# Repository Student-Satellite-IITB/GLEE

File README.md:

# GLEE
## Spectroscopy Payload
**Aim -** To validate the presence of minerals in the lunar regolith through gamma ray or x-ray spectroscopy.

**Tasks:**
- Designing a capable spectroscopy system
- Testing the precision of spectral lines
- Modelling known sources of radiation and their spectrum
- Data analysis and inference
### Circuit Design

The Circuit Consists of the following parts-
- Diode Sensor & Voltage Bias
- Charge Sensitive Preamplifier
- Pulse Shaper Circuit
- Baseline Restorer & Pole-Zero Cancellation
- Amplifier
- Multi-Channel Analyzer

### Diode Sensor

The X-rays and gamma rays coming from Sun, hit the lunar surface and are reflected by the lunar regolith. The photons from the reflected rays hit our sensor and produce a surge in the reverse current. The magnitude of this surge is used to estimate the composition of the lunar soil. We have decided to use photodiode sensors for the the task due to lower power consumption and small size as compared to other detectors. 

After going through the response rates of various diodes, the following 2 photodiode detectors were finalized:
- UM 9441: https://www.microsemi.com/existing-parts/parts/82558#resources
- X1007: https://www.mouser.in/datasheet/2/313/FirstSensor_09202018_X100-7_SMD_501401-1483097.pdf

While UM9441 is a radiation hardened diode, X1007 has prior spectroscopy usage. Both diodes need to have a reverse biased voltage of around 30 V in order to act as photodiode. 
The output voltage from the GLEE solar panel is expected to be 5 V, hence a boost convertor would be required to step up the voltage from 5 V to 30 V.

Selected Boost Convertor: **TPS6104x-Q1**  (https://www.ti.com/document-viewer/TPS61041-Q1/datasheet).
This boost convertor can step up voltage from 5 V to 28 V with an efficiency of 85 %, which was highest among the converters seen.

### Charge Sensitive Preamplifier

The next component in our system is the charge sensitive preamplifier, its task is to convert the current signal coming from the photodiode to a voltage signal which is easier to process and amplify. The output current from the photodiode is a **pulse train of dirac-delta signals** with each pulse representig an individual photon hitting the photodiode sensor. This current signal acts as the input signal for the CSP. The output of the CSP depends on the charge accumulated on it due to the photocurrent. The CSP can be thought as an integrator having current input and charge based voltage output.

The preamplifier basically consists of an Opamp, a pair of capacitors and a discharging mechanism. The CSP needs to regularly discharged in order to prevent it from getting saturated and/or saturating the final diode. We are using a resistance feedback CSP which uses the feedback resistance of the opamp to continously discharge the capacitor. The output voltage of this CSP is a **pulse train of exponential signals**. The height of each signal is directly propotional to the energy of the incident photons and time constant for this exponential signal is as per the values of feedback resistance and capacitance. The values of our feedback components are based on the count rate of the radiation. 

Count rate of a radiation for any sensor refers to the number of photons belonging to the energy range of that radiation that are hitting the sensor in a second.
- Count rate of X-rays = 
- Count rate of Gamma rays =

The time constant for the CSP has to be lesser than the one-fifth of the maximum count rate possible. For the CSP designed by us-
- Feedback Resistance (R) =
- Feedback Capacitance (C) =
- Time Constant (RC) =

Another possible alternative to this RF CSP would have been the transistor reset pre-amplifier, but it was rejected due to excessively complicated circuitry, higher power & size as compared to RF CSP and no significant benefits other than slight reduced noise.

Present COTS Opamp Models shortlisted for CSP-
- OPA656 : https://www.ti.com/document-viewer/OPA656/datasheet
- LMH6626 : https://www.ti.com/document-viewer/LMH6626/datasheet

### Pulse Shaper Circuit
The sensor is susceptible to noise and various forms of disturbances that cause deformation in the signal, therefore the signal needs to be filtered before it is sent to the amplifier in order to prevent amplification of unnecessary noise. The Pulse Shaper is basically a bandpass filter responsible for removing both the low and high frequency noises along with shaping the voltage signal in order to allow easier amplification and digitization. The input of the Pulse shaper is an **exponential voltage signal** obtained from CSP and the output is an **Gaussian voltage pulse**. A Gaussian shape minimizes the noise along with allowing easier digitization.

Our Pulse Shaper Circuit consists of one differentiator (high pass filter) and four integrators (low pass filter), with each of these sperated by a voltage follower in order to not cause any influence on each other. Use of four integrators as compared to one, significantly increases the shaping precision and therefore its recommended. Even 8 integrators may be used but were avoided in order to not further increase the size of circuit. The time constant of the integrators and the differentiators depend on the CSP time constant, and hence on the count rate of radiation. We have kept the sum of time constant of integrator same as that of the differentiator and the CSP. The exact values of capacitors and resistors used for this configuration were obtained after a lot of trial and error, until we were able to obtain optimum shaping. 
- Time Constant of integrators =
- Time Constant of differentiator =

The COTS components that we can use to build our Pulse Shaper :
- UA741 : https://www.ti.com/document-viewer/UA741/datasheet/features-slos0946106#SLOS0946106
- LM310 : https://circuits-diy.com/wp-content/uploads/2021/01/LM310N.pdf
- OP07 : https://www.ti.com/document-viewer/OP07/datasheet

### Baseline Restorer & Pole-Zero Cancellation
The Baseline restorer and pole-zero cancellation are not independent components but are additions to the pulse shaper in order to tackle the issues arising from the non idealities in the opamps that may lead to baseline shift, which is a constant offset voltage in addition to the required signal or it may cause ringing that leads to the signal not being able to reach a fixed value and keep oscillating around it.

to tackle such issues we have implemented these two corrective measures. The Pole zero restoration has been implemented alongside the differentiator with an extra resistance being added parallely to the capacitor there, meanwhile the baseline restorer requires an Opamp that  provides a negative feedbacks to any constant voltage present in the output signal and thus reducing it to zero.

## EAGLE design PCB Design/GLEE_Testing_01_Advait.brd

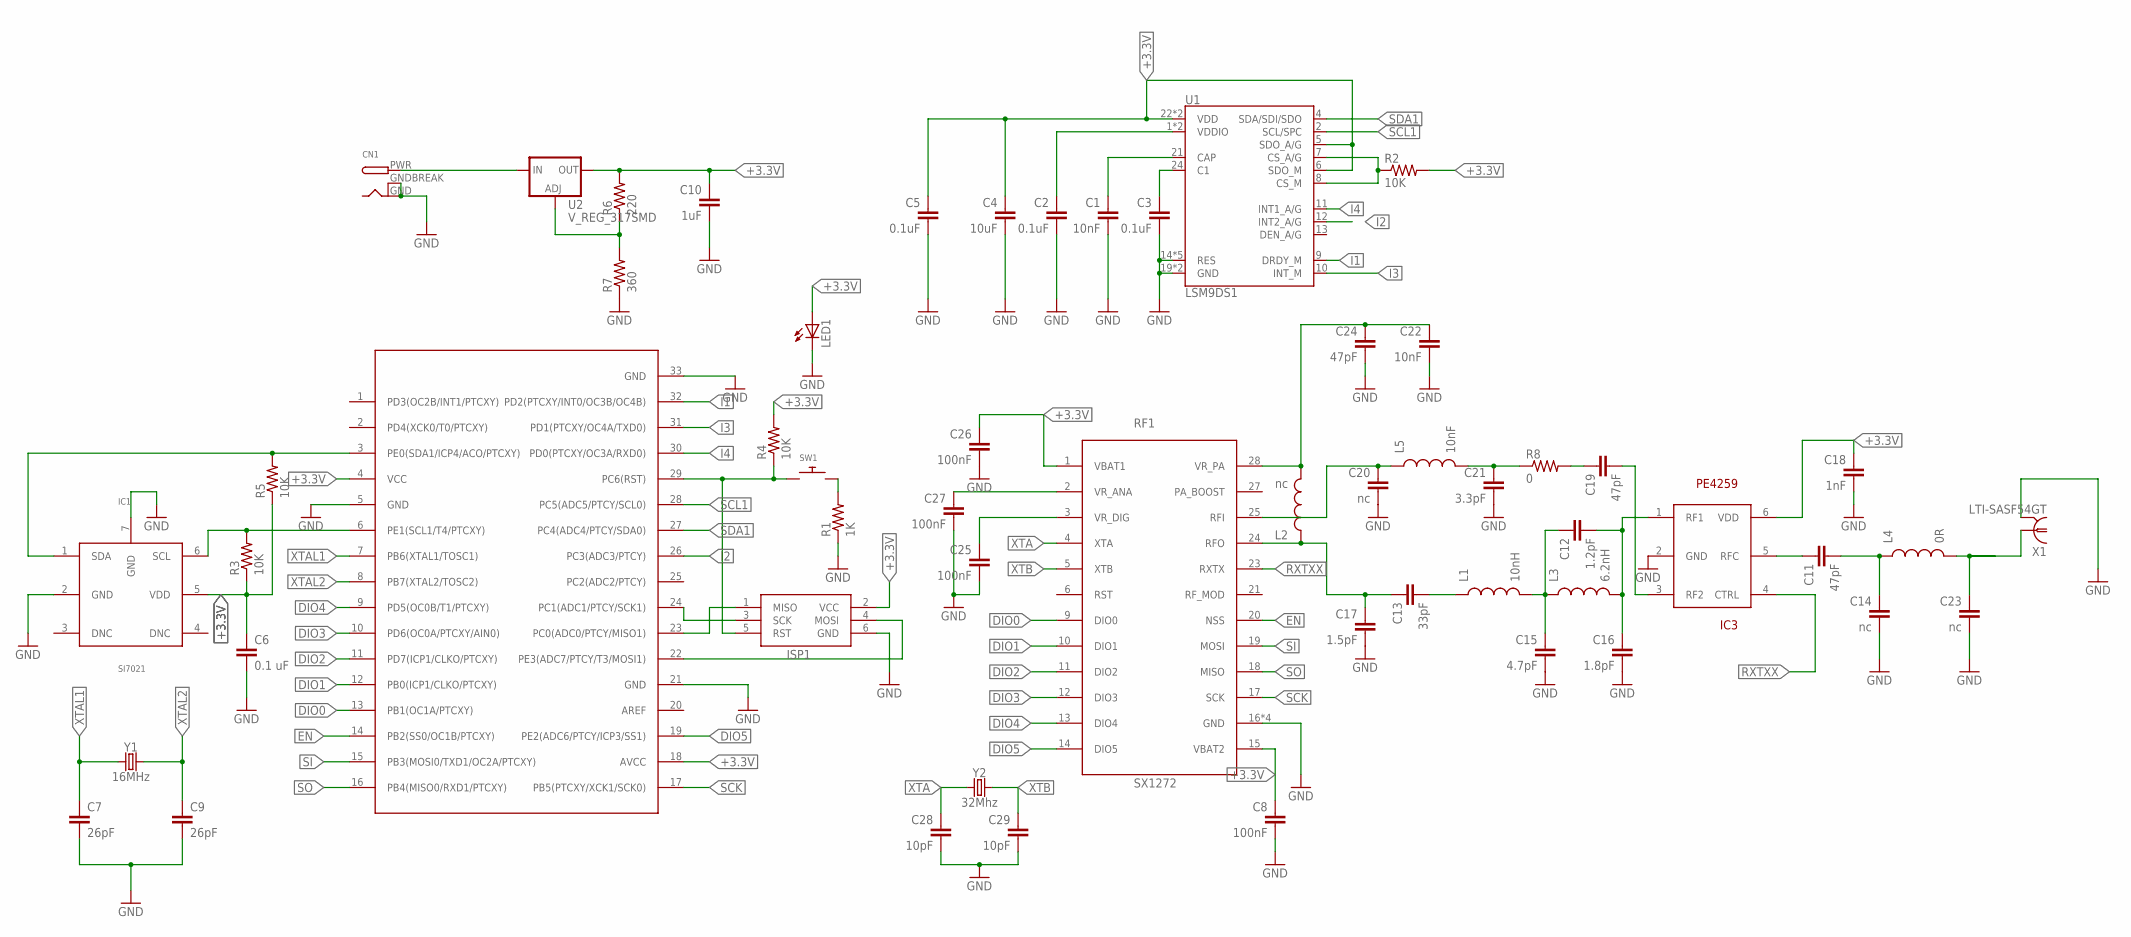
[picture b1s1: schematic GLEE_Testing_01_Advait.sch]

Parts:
C1, C22: 10nF; 0402-CAP
C2, C3, C5: 0.1uF; 0402-CAP
C4: 10uF; 0402-CAP
C6: 0.1 uF; 0402-CAP
C7, C9: 26pF; 0402-CAP
C8, C25, C26, C27: 100nF; 0402-CAP
C10: 1uF; 0402-CAP
C11, C19, C24: 47pF; 0402-CAP
C12: 1.2pF; 0402-CAP
C13: 33pF; 0402-CAP
C14, C20, C23: nc; 0402-CAP
C15: 4.7pF; 0402-CAP
C16: 1.8pF; 0402-CAP
C17: 1.5pF; 0402-CAP
C18: 1nF; 0402-CAP
C21: 3.3pF; 0402-CAP
C28, C29: 10pF; 0402-CAP
CN1: DCBARRELPTH; DCJACK_2MM_PTH
IC1: SI7021
IC2: ATMEGA328-PB
IC3: PE4259
ISP1: AVRISP-6; AVRISP
L1: 10nH; C0402
L2: nc; C0402
L3: 6.2nH; C0402
L4: 0R; C0402
L5: 10nF; C0402
LED1: LEDCHIPLED_0805; CHIPLED_0805
R1: 1K; 0402-RES
R2, R3, R4, R5: 10K; 0402-RES
R6: 220; 0402-RES
R7: 360; 0402-RES
R8: 0; 0402-RES
RF1: SX1272
SW1: SWITCH_PUSHBUTTONSOFTTOUCHSMD_SJ; PUSHBUTTON_SMD_SJ
U1: LSM9DS1; LGA24-8X4
U2: V_REG_317SMD; SOT223
X1: LTI-SASF54GT
Y1: 16MHz; CRYSTAL-SMD-2.0X1.6MM
Y2: 32Mhz; CRYSTAL-SMD-2.0X1.6MM

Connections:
DIO0: IC2.13 (PB1(OC1A/PTCXY)), RF1.9 (DIO0)
DIO1: IC2.12 (PB0(ICP1/CLKO/PTCXY)), RF1.10 (DIO1)
DIO2: IC2.11 (PD7(ICP1/CLKO/PTCXY)), RF1.11 (DIO2)
DIO3: IC2.10 (PD6(OC0A/PTCXY/AIN0)), RF1.12 (DIO3)
DIO4: IC2.9 (PD5(OC0B/T1/PTCXY)), RF1.13 (DIO4)
DIO5: IC2.19 (PE2(ADC6/PTCY/ICP3/SS1)), RF1.14 (DIO5)
EN: IC2.14 (PB2(SS0/OC1B/PTCXY)), RF1.20 (NSS)
GND: C1.2, C2.2, C3.2, C4.2, C5.2, C6.2, C7.2, C8.2, C9.2, C10.2, C14.2, C15.2, C16.2, C17.2, C18.2, C20.2, C21.2, C22.2, C23.2, C24.2, C25.2, C26.2, C27.2, C28.2, C29.2, CN1.GND, CN1.GNDBREAK, IC1.2 (GND), IC1.7 (GND), IC2.5 (GND), IC2.21 (GND), IC2.33 (GND), IC3.2 (GND), ISP1.6 (GND), LED1.C, R1.1, R7.1, RF1.16 (GND), RF1.22 (GND), RF1.26 (GND), RF1.29 (GND), U1.14 (RES), U1.15 (RES), U1.16 (RES), U1.17 (RES), U1.18 (RES), U1.19 (GND), U1.20 (GND), X1.2, X1.3 (2), X1.4 (2), X1.5 (2); also elsewhere on the board
I1: IC2.32 (PD2(PTCXY/INT0/OC3B/OC4B)), U1.9 (DRDY_M)
I2: IC2.26 (PC3(ADC3/PTCY)), U1.12 (INT2_A/G)
I3: IC2.31 (PD1(PTCXY/OC4A/TXD0)), U1.10 (INT_M)
I4: IC2.30 (PD0(PTCXY/OC3A/RXD0)), U1.11 (INT1_A/G)
unnamed: C19.1, R8.2
unnamed: C22.1, C24.1, L2.2, RF1.28 (VR_PA)
unnamed: CN1.PWR, U2.3 (IN)
unnamed: C19.2, IC3.3 (RF2)
unnamed: R2.1, U1.7 (CS_A/G), U1.8 (CS_M)
unnamed: R6.1, R7.2, U2.1 (ADJ)
unnamed: C20.1, L5.1, RF1.25 (RFI)
unnamed: C1.1, U1.21 (CAP)
unnamed: C2.1, U1.1 (VDDIO), U1.3 (VDDIO)
unnamed: C21.1, L5.2, R8.1
unnamed: C13.1, C17.1, L2.1, RF1.24 (RFO)
unnamed: C12.1, C15.1, L1.2, L3.1
unnamed: C13.2, L1.1
unnamed: C12.2, C16.1, IC3.1 (RF1), L3.2
unnamed: C23.1, L4.2, X1.1
unnamed: C11.1, IC3.5 (RFC)
unnamed: C3.1, U1.24 (C1)
unnamed: C11.2, C14.1, L4.1
unnamed: IC2.29 (PC6(RST)), ISP1.5 (RST), R4.1, SW1.P$1
unnamed: IC2.24 (PC1(ADC1/PTCY/SCK1)), ISP1.3 (SCK)
unnamed: C27.1, RF1.2 (VR_ANA)
unnamed: C25.1, RF1.3 (VR_DIG)
unnamed: IC2.23 (PC0(ADC0/PTCY/MISO1)), ISP1.1 (MISO)
unnamed: IC2.22 (PE3(ADC7/PTCY/T3/MOSI1)), ISP1.4 (MOSI)
unnamed: R1.2, SW1.P$2
RXTXX: IC3.4 (CTRL), RF1.23 (RXTX)
SCK: IC2.17 (PB5(PTCXY/XCK1/SCK0)), RF1.17 (SCK)
SCL: IC1.6 (SCL), IC2.6 (PE1(SCL1/T4/PTCXY)), R3.2
SCL1: IC2.28 (PC5(ADC5/PTCY/SCL0)), U1.2 (SCL/SPC)
SDA: IC1.1 (SDA), IC2.3 (PE0(SDA1/ICP4/ACO/PTCXY)), R5.2
SDA1: IC2.27 (PC4(ADC4/PTCY/SDA0)), U1.4 (SDA/SDI/SDO)
SI: IC2.15 (PB3(MOSI0/TXD1/OC2A/PTCXY)), RF1.19 (MOSI)
SO: IC2.16 (PB4(MISO0/RXD1/PTCXY)), RF1.18 (MISO)
XTA: C28.1, RF1.4 (XTA), Y2.1
XTAL1: C7.1, IC2.7 (PB6(XTAL1/TOSC1)), Y1.1
XTAL2: C9.1, IC2.8 (PB7(XTAL2/TOSC2)), Y1.3 (2)
XTB: C29.1, RF1.5 (XTB), Y2.3 (2)

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
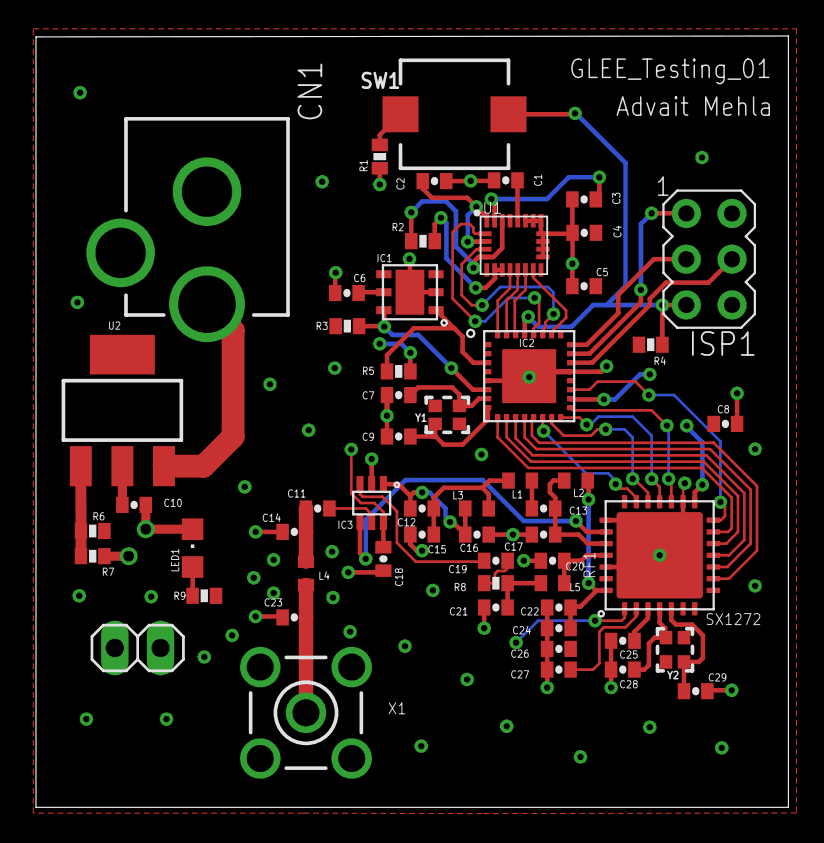
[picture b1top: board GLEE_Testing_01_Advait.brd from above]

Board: 2 copper layers, 41.8 x 42.9 mm, 57 parts (0 on the bottom side), 51 nets.

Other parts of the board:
JP6: 1X02
R9: 100; 0402-RES

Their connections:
GND: JP6.1; also elsewhere on the board

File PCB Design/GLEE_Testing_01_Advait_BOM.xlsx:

Part | Value | Device | Package | Description | Comments
C1 | 10nF | CAP0402-CAP | 0402-CAP | Capacitor
C2 | 0.1uF | CAP0402-CAP | 0402-CAP | Capacitor
C3 | 0.1uF | CAP0402-CAP | 0402-CAP | Capacitor
C4 | 10uF | CAP0402-CAP | 0402-CAP | Capacitor
C5 | 0.1uF | CAP0402-CAP | 0402-CAP | Capacitor
C6 | 0.1 uF | CAP0402-CAP | 0402-CAP | Capacitor
C7 | 26pF | CAP0402-CAP | 0402-CAP | Capacitor
C8 | 100nF | CAP0402-CAP | 0402-CAP | Capacitor
C9 | 26pF | CAP0402-CAP | 0402-CAP | Capacitor
C10 | 1uF | CAP0402-CAP | 0402-CAP | Capacitor
C11 | 47pF | CAP0402-CAP | 0402-CAP | Capacitor
C12 | 1.2pF | CAP0402-CAP | 0402-CAP | Capacitor
C13 | 33pF | CAP0402-CAP | 0402-CAP | Capacitor
C14 | nc | CAP0402-CAP | 0402-CAP | Capacitor
C15 | 4.7pF | CAP0402-CAP | 0402-CAP | Capacitor
C16 | 1.8pF | CAP0402-CAP | 0402-CAP | Capacitor
C17 | 1.5pF | CAP0402-CAP | 0402-CAP | Capacitor
C18 | 1nF | CAP0402-CAP | 0402-CAP | Capacitor
C19 | 47pF | CAP0402-CAP | 0402-CAP | Capacitor
C20 | nc | CAP0402-CAP | 0402-CAP | Capacitor
C21 | 3.3pF | CAP0402-CAP | 0402-CAP | Capacitor
C22 | 10nF | CAP0402-CAP | 0402-CAP | Capacitor
C23 | nc | CAP0402-CAP | 0402-CAP | Capacitor
C24 | 47pF | CAP0402-CAP | 0402-CAP | Capacitor
C25 | 100nF | CAP0402-CAP | 0402-CAP | Capacitor
C26 | 100nF | CAP0402-CAP | 0402-CAP | Capacitor
C27 | 100nF | CAP0402-CAP | 0402-CAP | Capacitor
C28 | 10pF | CAP0402-CAP | 0402-CAP | Capacitor
C29 | 10pF | CAP0402-CAP | 0402-CAP | Capacitor
CN1 |  | DCBARRELPTH | DCJACK_2MM_PTH | 2.0mm DC Barrel Jack
IC1 | SI7021 | SI7021 | SI7021 - A20
IC2 | ATMEGA328-PB | ATMEGA328-PB | 32-pin 32MS1
IC3 | PE4259 | PE4259 | 6-lead SC-70
ISP1 | AVRISP-6 | AVRISP-6 | AVRISP | AVR ISP HEADER
L1 | 10nH | INDUCTOR0402 | C0402 | Inductors
L2 | nc | INDUCTOR0402 | C0402 | Inductors
L3 | 6.2nH | INDUCTOR0402 | C0402 | Inductors
L4 | 0R | INDUCTOR0402 | C0402 | Inductors | Zero Ohm Resistor
L5 | 10nF | INDUCTOR0402 | C0402 | Inductors
LED1 |  | LEDCHIPLED_0805 | CHIPLED_0805 | LED
R1 | 1K | RESISTOR0402-RES | 0402-RES | Resistor
R2 | 10K | RESISTOR0402-RES | 0402-RES | Resistor
R3 | 10K | RESISTOR0402-RES | 0402-RES | Resistor
R4 | 10K | RESISTOR0402-RES | 0402-RES | Resistor
R5 | 10K | RESISTOR0402-RES | 0402-RES | Resistor
R6 | 220 | RESISTOR0402-RES | 0402-RES | Resistor
R7 | 360 | RESISTOR0402-RES | 0402-RES | Resistor
R8 | 0 | RESISTOR0402-RES | 0402-RES | Resistor
RF1 | SX1272 | SX1272 | 28-lead QFN
SW1 |  | SWITCH_PUSHBUTTONSOFTTOUCHSMD_SJ | PUSHBUTTON_SMD_SJ | Buttons
U1 | LSM9DS1 | LSM9DS1 | LGA24-8X4 | LSM9DS1 3D accelerometer, gyroscope & magnetometer
U2 | V_REG_317SMD | V_REG_317SMD | SOT223 | Voltage Regulator
X1 | LTI-SASF54GT | LTI-SASF54GT | LTI-SASF54GT | SMA vertical PCB through hole jack
Y1 | 16MHz | CRYSTAL-16MHZSMD-2X1.6 | CRYSTAL-SMD-2.0X1.6MM | 16MHz Crystal
Y2 | 32Mhz | CRYSTAL-16MHZSMD-2X1.6 | CRYSTAL-SMD-2.0X1.6MM | 16MHz Crystal

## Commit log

2020-03-14 Added codes for data analysis
    elecentro.dat-Data file of earthquake data
    Project_Elecentro.ipynb-Project codes
    Test_cases.ipynb-Test cases for functions used in project.
2020-04-22 updated codes for seismic responsse spectrum
2021-06-25 Rename README.md to SRS_Elcentro/README.md
2021-06-25 Rename Project_Elecentro.ipynb to SRS_Elcentro/Project_Elecentro.ipynb
2021-06-25 Test cases for functions in shock response spectrum
2021-06-25 Data file used in code
2021-06-27 EW data for elcentro earthquake
2021-06-27 data for elcentro earthquake
2021-06-27 data from phone accelerometer
2021-06-27 Code for micrometeoroid detection
2021-06-27 Implementing a simple algorithm for P and S wave
2021-06-27 Codes for marking P and S wave onset, sta/lta exploration
2021-06-27 Updated codes for p and s wave onset marking
2021-06-27 Data file for ground vibration
2021-06-27 Rename groundvib.csv to Ground_data_test/groundvib.csv
2021-06-27 Testing code with data collected from ground with phone accelerometer
2021-06-27 A 2D elastic model for wave propagation
2021-06-27 2D elastic model with explosive source at the centre of the domain
2021-06-27 3D elastic model with explosive source at the centre of domain
2021-06-27 Elastic model creation using demo_model object
2021-06-27 Acoustic model with subdomains based boundary implementation
2021-06-27 A simple 2D acoustic model
2021-06-27 3D model with damping boundary conditions
2021-06-27 3D elastic model with no damping boundary conditions
2021-06-27 Elastic model using subdomains
2021-06-27 Output file for relation between source and energy
2021-06-27 2D elastic model with vert force source at top
2021-06-27 3D elastic model with vert source at the top
2021-06-27 Checking relation between rms value and source amplitude
2021-06-27 Code for relation between energy and source amplitude
2021-06-27 3D model with source injected in stress field
2021-06-27 TDOA based source localization implementation
2021-06-30 Source localization with TDOA
    Implementation of time difference of arrival technique to localize the source.
2021-07-03 TDOA based source localization
    Time difference of arrival-based source localization
2021-07-07 Iterating over both receiver and source position
2021-07-07 Iteration over receiver and source position
2021-07-10 Iterating positions of receivers along with the source
2021-07-15 Error calculation for large number of receivers
2021-07-17 correction in last block
2021-07-28 Source localization starting with mean position
2021-07-31 Restricting domain by average time from receivers
2021-08-14 Nearest neighbour and tangent points
2021-08-14 Rename Multiple sources.ipynb to Multiple Sources/NearestNeighbour_TangentPoints_sortingFunction.ipynb
2021-08-18 Grey wolf optimization code for localization
2021-08-18 Rename Grey_wolf_optimization.ipynb to Optimization/Grey_wolf_optimization.ipynb
2021-08-21 Using grey wolf optimization to deduce receivers and source positions
2021-08-21 Adding Si_7021 code(Adithya Raj)
2021-08-21 Rename main.cpp to Si7021_Adithya.cpp
2021-08-22 Updated code for GWO
    A small correction made in value of A2
2021-08-25 Updated code anf graphs for GWO
2021-08-25 Create Si7021_Akshat.c
    A temporary file that has code to read temperature value from the sensor in no master hold mode
2021-08-26 Add register mapping
2021-08-28 Added modified fitness function for GWO
2021-09-01 GWO with sorted TDOA implementation
2021-09-01 Add LSM9DS1.c
    Contains definition of the functions declared in LSM9DS1.h file
2021-09-01 Declare LSM9DS1 functions
2021-09-01 Added functions declarations and commands
2021-09-03 Added testing PCB
2021-09-04 Add functions to initialize accelerometer and read data
    uC reads data from sensor as and when available (bypass mode)
2021-09-04 Add functions to read and write to register
2021-09-04 Updated the code
    Modified the configure_acc and stop function.
    Intended the return values.
2021-09-04 Added magnetometer register mapping code
2021-09-04 Wrote function for whale optimization algorithm
2021-09-04 Completed board design, ERC and finishing touches pending
2021-09-22 trigger algorithm for wave onset using sta-lta
    wave onset trigger using sta lta on modified data
2021-09-22 Rename sta-lta.ipynb to wave_onset/sta-lta.ipynb
2021-09-22 Completed first iteration of this board
    Ready for QA
2021-09-22 New folder created to upload my code
    A sample text file is added in the folder to make it.
2021-09-22 LSM9DS1 code files uploaded
    All the code written together for the sensor is uploaded in the new folder.
2021-09-22 Declare FIFO functions
    FIFO_init() to initialize FIFO mode, acc_data_available_FIFO() to check if unread samples available in FIFO
2021-09-22 Define FIFO-related functions
2021-09-22 Include FIFO related functionality(commented out)
2021-09-23 Updated Measurement Function
2021-10-06 Added 3 FIFO modes and magneto, gyro functions
    A rough code of the remaining 3 FIFO modes is added. The first iteration of initialization and reading data from gyroscope and magnetometer is added.
2021-10-06 Create Sample
2021-10-06 Add files via upload
    added hold
2021-10-06 GWO for multiple initial configurations
2021-10-06 GWO for multiple initial configuration with modified error function
2021-10-09 Add files via upload
    First try to correct WO code
2021-10-16 Add files via upload
    second correction, fitness vs no. of iteration graph
2021-10-16 Add files via upload
    3rd version, changing component based iteration conditions to to vector conditions
2021-10-16 Integrating energy calculation with sta-lta onset detection
2021-10-20 Corrected fitness function for WOA
    Other modifications have also been made in the updating part.
2021-10-22 Blocks to update whales modified
    All "if" conditions changed to vectors, update equations cross verified, results not as expected, limiting the whales left, b may vary
2021-10-23 receiver and estimated source plots
    Receivers final and initial plots, estimated source position plots, results not good.
2021-10-24 Removed SMD Antenna and made a few other changes after preliminary QA
2021-10-24 Final QA
    Added a few changes, updated filenames, added library and BOM
2021-10-25 Added to Optimization folder
2021-10-25 Whale Optimization with Bounds on Receivers
    Domain Bounds on receivers( not individual), Bound on Source position according to TOA, Plot of Estimated vs initial source, estimated vs initial receivers, error plot
2021-10-25 Delete Whale_optimization_algorithm_edited.ipynb
    Modified and added to Optimization Folder
2021-10-30 Revert "Add files via upload"
2021-10-30 implemented individual bounds on receivers
    bounds on dynamic positions
2021-10-30 Individual bounds on receivers wrt initial position
2021-10-30 Update main.c to add continuous mode
2021-10-30 Declare Continuous mode related functions
2021-10-30 Define Continuous mode related functions
2021-10-30 GWO implementation with sorted data
2021-10-30 Update main.c to bypass mode (for testing)
2021-11-23 declare functions for interrupt generation
2021-11-23 define function for interrupt generation
2021-11-23 Add ISR, function to configure external interrupts
2021-11-23 Added pins for voltage testing
2021-11-23 Added external Interrupt functions, ISR
2021-11-27 Beamforming with exact receiver positions
2021-11-27 Beamforming for exact receiver positions
2021-11-27 Data files for beamforming
2021-11-29 Data file for beamforming
2021-11-29 First Run, Minimize sum of square error
2021-11-30 Iteration over phi,
    2nd Run, iteration on phi, good results
2021-12-02 to be QAed, final results with ideal time recordings
2021-12-02 to be QAed, plane wave fitting on ideal data
2021-12-04 Plane wave fitting by Subsets
    Divide Circle in odd and even indices, implement plane wave fitting for each, results matching
2021-12-04 first version for estimating velocity by plane wave fitting
    code in eary stage, results not accurate
2021-12-05 FK analysis with receivers subsets
2021-12-05 Data for a circular arrangement used in subset implementation
2021-12-06 Velocity estimation and concurrency of estimates
    good results from them, deleted the change of reference frame logic from error_in_concurrency()
2021-12-06 Unknown velocity estimated closely
2021-12-09 less than 10% error in velocity
2021-12-10 Shifted whale optimization code to designated folder
2021-12-10 FK analysis subset implementation updated
    Properly created random and sequenced subsets and compared their mean and modal values.
2021-12-11 to be QAed
2021-12-11 true velocity set to 2000m/s
2021-12-11 Choosing the backazimuth value based on a probabale velocity range
2021-12-13 attempt
2021-12-13 to be QAed, commented functions
2021-12-13 added mean position on plot
2021-12-13 defined function to return mean time of arrival
2021-12-13 QA comments implemented
2021-12-13 Added current progress
2021-12-14 backazimuth approximated at vel =2000m/s
2021-12-14 velocity estimation on simulated data
2021-12-14 Completed learning of SPI by demonstrating all transmission directions
2021-12-14 Data with high sampling frequency
2021-12-14 High sampling rate data
2021-12-14 Rename Beamforming/recx_pos_circ.csv to Beamforming/High_sampling_rate_data/recx_pos_circ.csv
2021-12-14 High sampling rate(405Hz) simulated data
2021-12-14 File used for data generation
2021-12-14 Data for testing plain wave fitting
2021-12-21 Created readme file for description
2021-12-22 FK analysis subsets implementation with velocity restriction
2021-12-22 Error addition in receiver positions FK analysis
2021-12-24 Velocity estimation code dropped into folder
2021-12-24 Transceiver SX1272 Code sample text file
2021-12-24 Rename sample to README.md
2021-12-24 estimated velocity by data on receivers on backazimuth
2021-12-24 SPI initialize, Register address mapping
2021-12-24 Reducing input data by TOA
2021-12-24 Time of arrival functions in .py file
2021-12-27 Added register value mapping code
2021-12-28 Add files via upload
    Header Files for SX1272 functions
2021-12-28 C source code for SX1272 functions
2021-12-28 define UART related functions
2021-12-28 Modified functions, merge two code files in one
    Merged the code files written by me and Adithya in one and created a new header file for the transceiver. Edited a few functions.
2021-12-29 uploaded files with code for time of arrival and energy calculation
2021-12-29 uploaded file has code for time of arrival and energy calculation
2022-01-01 Implemented TDOA in sector containing backazimuth
2022-01-03 inverted sign of random time recordings
2022-01-07 Add additional comments
2022-01-12 Transceiver Tx code
    Changed the register mapping code, added the Tx Fifo mode function, and properly defined the main function.
2022-01-14 Complete Reception code of the transceiver
    Added the RXFIFO function and RXSettings array, modified the read register function and main.c file
2022-01-19 Adding Transmit function
2022-01-19 Correcting errors in transmit function
2022-01-22 Edited variable/function names by QA guidelines
2022-01-29 Readme for reading apollo data
2022-01-29 Rename readme.txt to ALSEP_data/readme.txt
2022-01-29 Raw data file uploaded
2022-02-01 Added Geant4 work
2022-02-01 Renamed folder
2022-02-01 Changed readme
2022-03-23 Updated link for file with only data
2022-03-26 Uploaded extracted data files
2022-03-26 code to extract data from pse_a_11 text file
2022-03-26 extract data from pse_a11_1
2022-03-26 code to extract data from the pse_a11_1 text file
2022-03-26 to be uploaded in seismology branch
2022-04-08 this is test code for thumper data
2022-05-02 Update GLEE_Si7021.h
    Completed except checksum
2022-05-02 Update GLEE_Si7021.h
    Header updated
2022-05-02 Create GLEE_Si7021.cpp
    Almost finished except checksum

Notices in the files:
parts and their libraries:
SparkFun: Licensing: CC v3.0 Share-Alike You are welcome to use this library for commercial purposes.
SparkFun-Clocks: Licensing: Creative Commons ShareAlike 4.0 International - https://creativecommons.org/licenses/by-sa/4.0
